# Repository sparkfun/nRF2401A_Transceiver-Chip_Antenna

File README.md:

nRF2401A Transceiver - Chip Antenna
=================================
[  
*Transceiver nRF2401A with Chip Antenna (WRL-00152)*](https://www.sparkfun.com/products/152)

This is a breakout board for the nRF2401A 2.4GHz transceiver module with a built-in chip antenna. 

Repository Contents
-------------------
* **/Firmware** - Example firmware to use with the chip
* **/Hardware** - All Eagle design files (.brd, .sch)

License Information
-------------------
The hardware is released under [Creative Commons Share-alike 3.0](http://creativecommons.org/licenses/by-sa/3.0/).  
All other code is open source so please feel free to do anything you want with it; 
you buy me a beer if you use this and we meet someday ([Beerware license](http://en.wikipedia.org/wiki/Beerware)).

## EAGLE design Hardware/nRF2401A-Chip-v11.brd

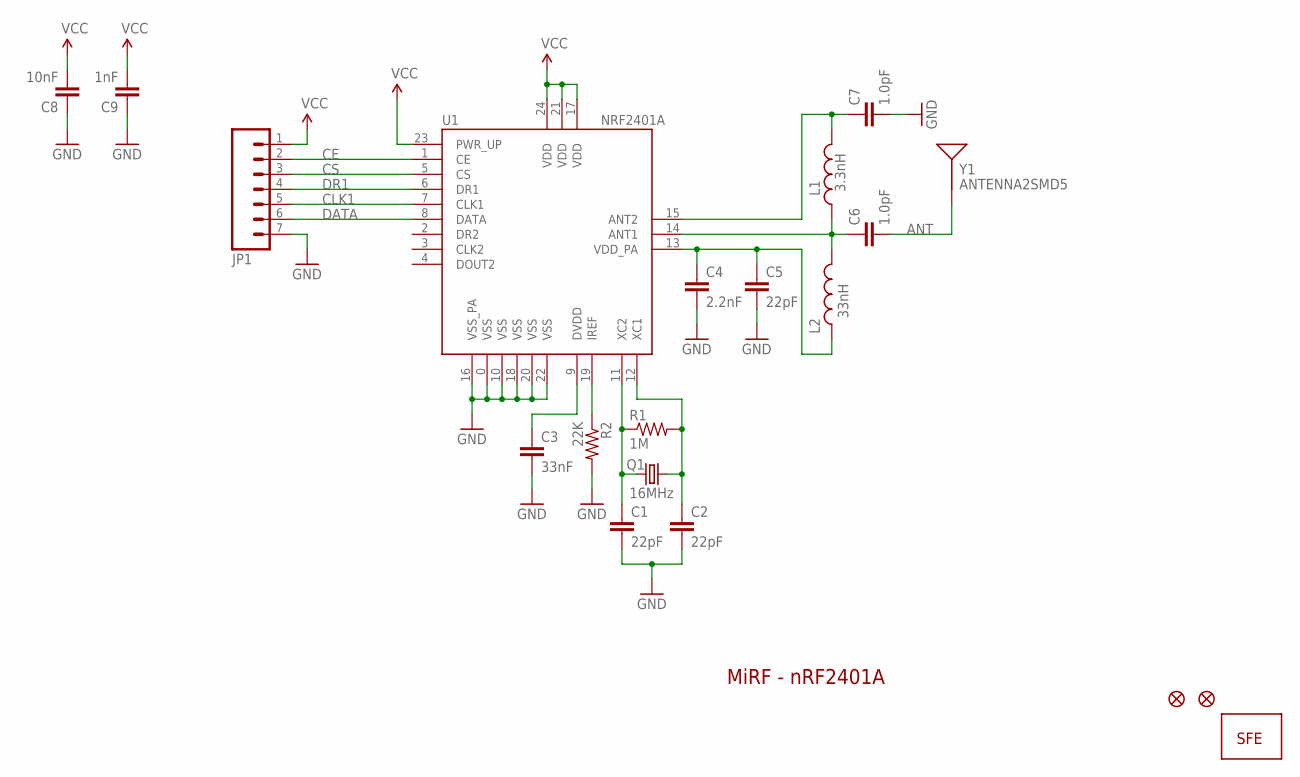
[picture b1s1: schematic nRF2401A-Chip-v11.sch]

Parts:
C1, C2, C5: 22pF; C0402
C3: 33nF; C0402
C4: 2.2nF; C0402
C6, C7: 1.0pF; C0402
C8: 10nF; C0402
C9: 1nF; C0402
JP1: M07; 1X07
JP2, JP3: FIDUCIALUFIDUCIAL; MICRO-FIDUCIAL
L1: 3.3nH; C0402
L2: 33nH; C0402
Q1: 16MHz; CRYSTAL-SMD-5X3
R1: 1M; C0402
R2: 22K; C0402
U1: NRF2401A; MLP-24
U$1: LOGO-SFESK; SFE-LOGO-FLAME
Y1: ANTENNA2SMD5; ANTENNA-CHIP5

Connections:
ANT: C6.2, Y1.FEED
CE: JP1.2, U1.1 (CE)
CLK1: JP1.5, U1.7 (CLK1)
CS: JP1.3, U1.5 (CS)
DATA: JP1.6, U1.8 (DATA)
DR1: JP1.4, U1.6 (DR1)
GND: C1.2, C2.2, C3.2, C4.2, C5.2, C7.2, C8.1, C9.1, JP1.7, R2.2, U1.0 (VSS), U1.10 (VSS), U1.16 (VSS_PA), U1.18 (VSS), U1.20 (VSS), U1.22 (VSS)
unnamed: C1.1, Q1.1, R1.1, U1.11 (XC2)
unnamed: C2.1, Q1.3 (2), R1.2, U1.12 (XC1)
unnamed: C6.1, L1.1, L2.2, U1.14 (ANT1)
unnamed: R2.1, U1.19 (IREF)
unnamed: C3.1, U1.9 (DVDD)
unnamed: C7.1, L1.2, U1.15 (ANT2)
unnamed: C4.1, C5.1, L2.1, U1.13 (VDD_PA)
VCC: C8.2, C9.2, JP1.1, U1.17 (VDD), U1.21 (VDD), U1.23 (PWR_UP), U1.24 (VDD)

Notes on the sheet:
MiRF - nRF2401A

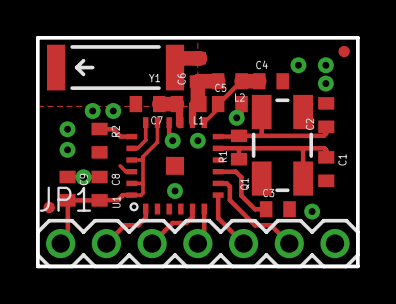
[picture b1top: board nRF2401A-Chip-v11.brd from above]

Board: 2 copper layers, 17.8 x 12.7 mm, 20 parts (1 on the bottom side), 15 nets.

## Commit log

2013-09-04 Initial repo commit
